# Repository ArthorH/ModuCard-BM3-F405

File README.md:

# Base module (Card) template project for ModuCard System

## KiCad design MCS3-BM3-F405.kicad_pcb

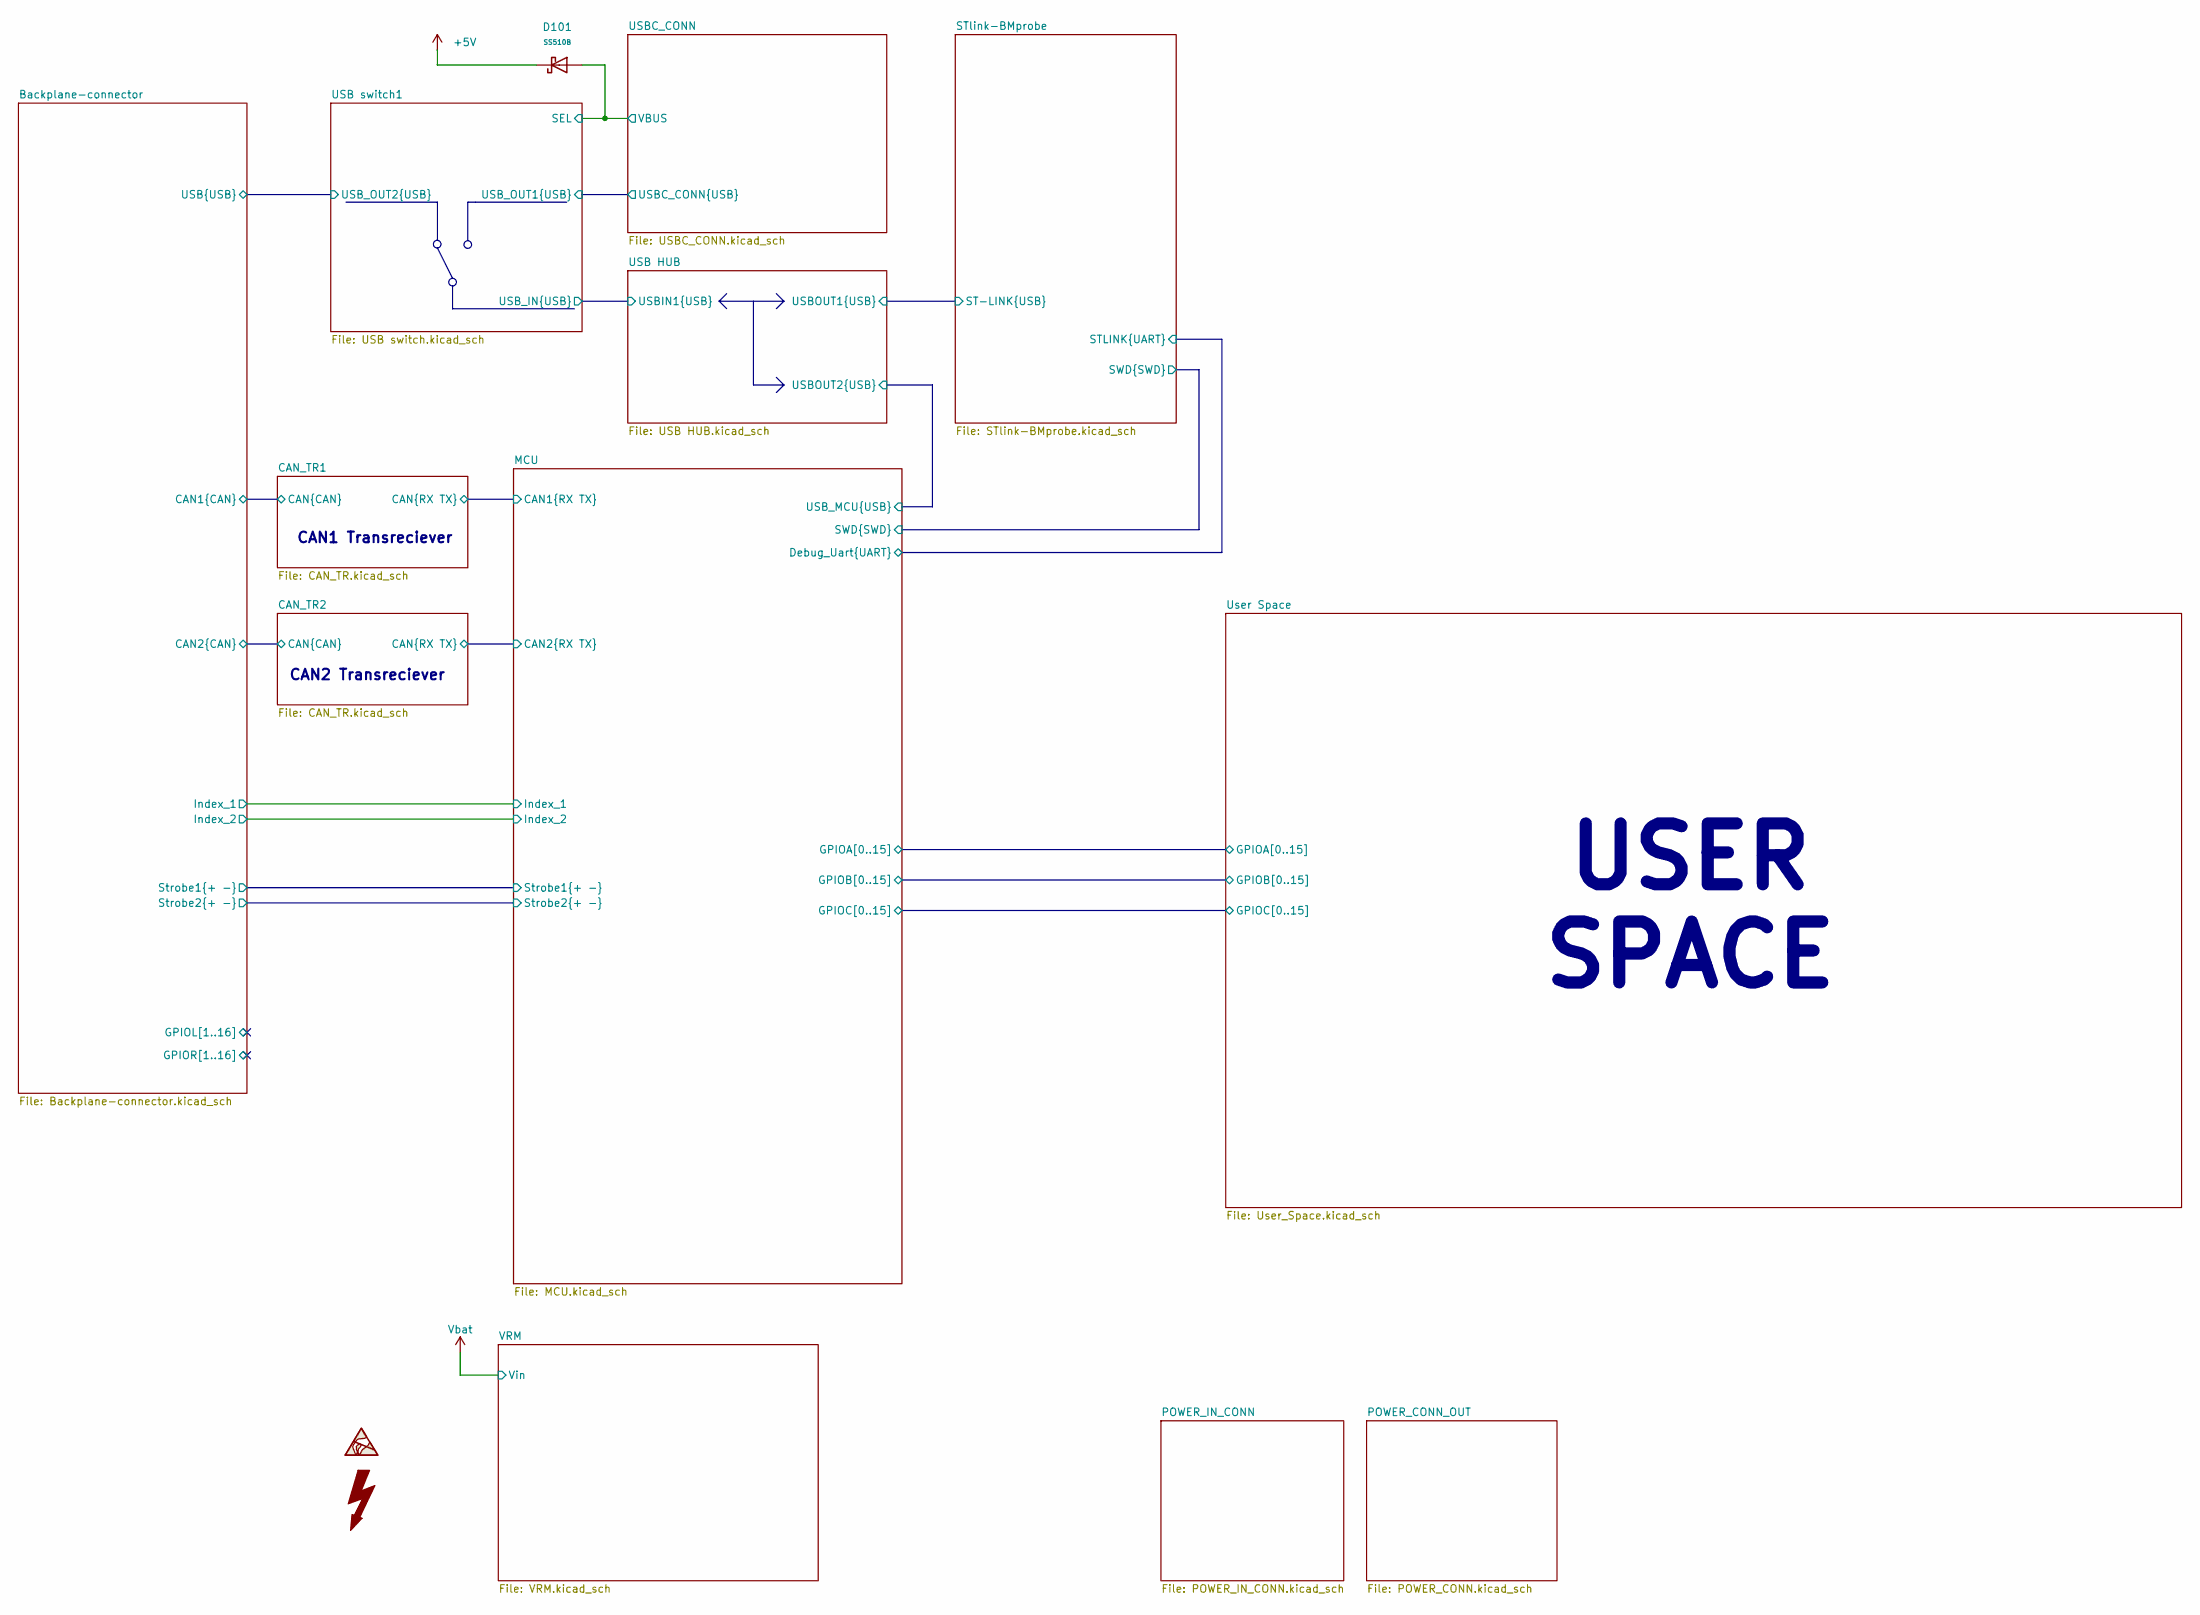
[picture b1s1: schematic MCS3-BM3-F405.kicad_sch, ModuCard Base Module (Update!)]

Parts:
D101: SS510B; D_SMB; Forward Voltage (Vf@If) 0.85V@5.0A; Reverse Voltage (Vr) 100V; Part SS510B; LCSC C7420368

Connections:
+5V: D101.1; also elsewhere on the board
VBUS: D101.2; also elsewhere on the board

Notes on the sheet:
USER SPACE
CAN2 Transreciever
CAN1 Transreciever

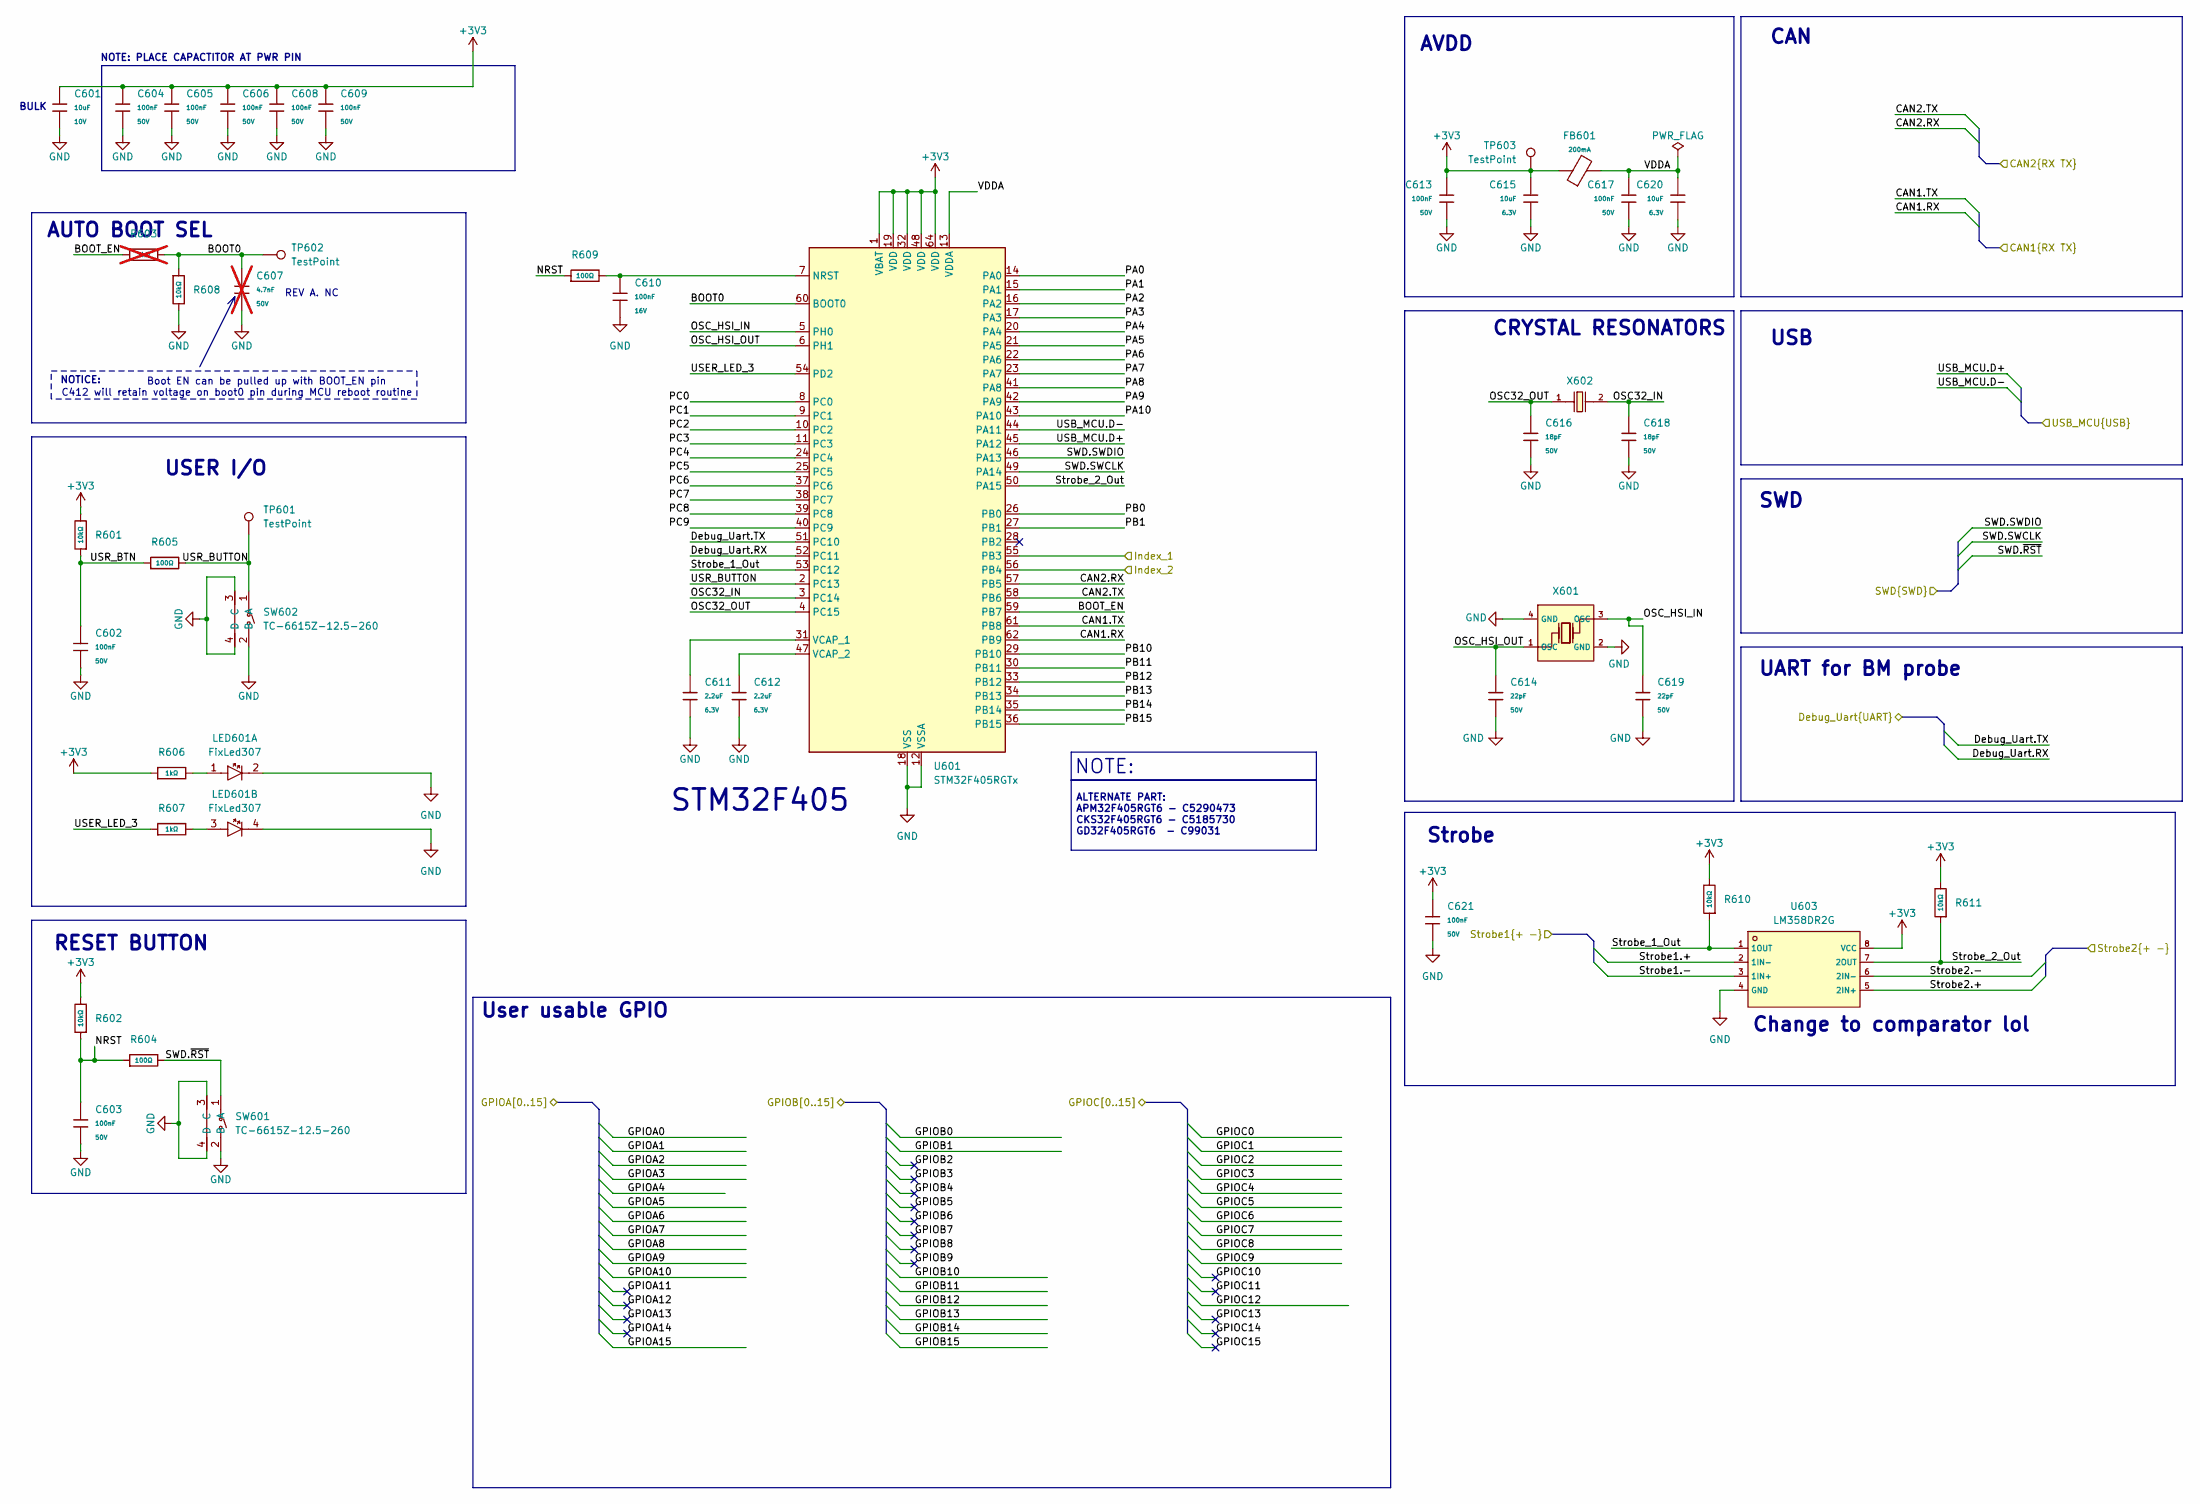
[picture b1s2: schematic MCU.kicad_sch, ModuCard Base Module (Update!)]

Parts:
C601: 10uF; C_0603; Voltage Rated 10V; Tolerance ±10%; Part CL10A106KP8NNNC; LCSC C19702
C602, C603, C604, C605, C606, C608, C609, C613, C617, C621: 100nF; C_0402; Voltage Rated 50V; Tolerance ±10%; Part CL05B104KB54PNC; LCSC C307331
C607: 4.7nF; C_0402; Voltage Rated 50V; Tolerance ±10%; Part 0402B472K500NT; LCSC C1538; not fitted
C610: 100nF; C_0402; Voltage Rated 16V; Tolerance ±10%; Part CL05B104KO5NNNC; LCSC C1525
C611, C612: 2.2uF; C_0402; Voltage Rated 6.3V; Tolerance ±20%; Part CL05A225MQ5NSNC; LCSC C12530
C614, C619: 22pF; C_0402; Voltage Rated 50V; Tolerance ±5%; Part 0402CG220J500NT; LCSC C1555
C615, C620: 10uF; C_0402; Voltage Rated 6.3V; Tolerance ±20%; Part CL05A106MQ5NUNC; LCSC C15525
C616, C618: 18pF; C_0402; Voltage Rated 50V; Tolerance ±5%; Part 0402CG180J500NT; LCSC C1549
FB601: FB_0603; Current Rating 200mA; Tolerance ±25%; Part GZ1608D601TF; LCSC C1002
LED601: FixLed307
R601, R602, R608, R610, R611: 10kΩ; R_0402; Overload Voltage (Max) 50V; Tolerance ±1%; Part 0402WGF1002TCE; LCSC C25744
R603: 1kΩ; R_0402; Overload Voltage (Max) 50V; Tolerance ±1%; Part 0402WGF1001TCE; LCSC C11702; not fitted
R604, R605, R609: 100Ω; R_0402; Overload Voltage (Max) 50V; Tolerance ±1%; Part 0402WGF1000TCE; LCSC C25076
R606, R607: 1kΩ; R_0402; Overload Voltage (Max) 50V; Tolerance ±1%; Part 0402WGF1001TCE; LCSC C11702
SW601, SW602: TC-6615Z-12.5-260; SW-TH_4P-L7.3-TC-6615Z-12.5-260; MPN TC-6615Z-12.5-260; LCSC Part C7528758
TP601, TP602, TP603: TestPoint; TestPoint_Pad_D1.0mm
U601: STM32F405RGTx; LQFP-64_10x10mm_P0.5mm; LCSC C15742
U603: LM358DR2G; SOIC-8_L5.0-W4.0-P1.27-LS6.0-BL; Part LM358DR2G; LCSC C7950
X601: X32258MOB4SI; OSC-SMD_4P-L3.2-W2.5-BL; Frequency Tolerance ±10ppm; Part X322525MOB4SI; LCSC C2682775
X602: Q13FC1350000400; FC-135R_L3.2-W1.5; Frequency Tolerance ±20ppm; Part Q13FC13500004; LCSC C97606

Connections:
+3V3: C601.1, C604.1, C605.1, C606.1, C608.1, C609.1, C613.1, C615.1, C621.1, FB601.1, R601.2, R602.2, R606.1, R610.2, R611.2, TP603.1, U601.1 (VBAT), U601.19 (VDD), U601.32 (VDD), U601.48 (VDD), U601.64 (VDD), U603.8 (VCC); also elsewhere on the board
/Backplane-connector/Index_1: U601.55 (PB3); also elsewhere on the board
/Backplane-connector/Index_2: U601.56 (PB4); also elsewhere on the board
/Backplane-connector/Strobe1.+: U603.2 (1IN-); also elsewhere on the board
/Backplane-connector/Strobe1.-: U603.3 (1IN+); also elsewhere on the board
/Backplane-connector/Strobe2.+: U603.5 (2IN+); also elsewhere on the board
/Backplane-connector/Strobe2.-: U603.6 (2IN-); also elsewhere on the board
/CAN_TR1/CAN.RX: U601.62 (PB9); also elsewhere on the board
/CAN_TR1/CAN.TX: U601.61 (PB8); also elsewhere on the board
/CAN_TR2/CAN.RX: U601.57 (PB5); also elsewhere on the board
/CAN_TR2/CAN.TX: U601.58 (PB6); also elsewhere on the board
/MCU/BOOT0: C607.1, R603.2, R608.1, TP602.1, U601.60 (BOOT0)
/MCU/BOOT_EN: R603.1, U601.59 (PB7)
/MCU/Debug_Uart.RX: U601.52 (PC11); also elsewhere on the board
/MCU/Debug_Uart.TX: U601.51 (PC10); also elsewhere on the board
/MCU/NRST: C603.1, R602.1, R604.1, R609.1
/MCU/OSC32_IN: C618.1, U601.3 (PC14), X602.2
/MCU/OSC32_OUT: C616.1, U601.4 (PC15), X602.1
/MCU/OSC_HSI_IN: C619.1, U601.5 (PH0), X601.3 (OSC)
/MCU/OSC_HSI_OUT: C614.1, U601.6 (PH1), X601.1 (OSC)
/MCU/PA0: U601.14 (PA0)
/MCU/PA1: U601.15 (PA1)
/MCU/PA2: U601.16 (PA2)
/MCU/PA3: U601.17 (PA3)
/MCU/PA4: U601.20 (PA4)
/MCU/PA5: U601.21 (PA5)
/MCU/PA6: U601.22 (PA6)
/MCU/PA7: U601.23 (PA7)
/MCU/PA8: U601.41 (PA8)
/MCU/PA9: U601.42 (PA9)
/MCU/PA10: U601.43 (PA10)
/MCU/PB0: U601.26 (PB0)
/MCU/PB1: U601.27 (PB1)
/MCU/PB10: U601.29 (PB10)
/MCU/PB11: U601.30 (PB11)
/MCU/PB12: U601.33 (PB12)
/MCU/PB13: U601.34 (PB13)
/MCU/PB14: U601.35 (PB14)
/MCU/PB15: U601.36 (PB15)
/MCU/PC0: U601.8 (PC0)
/MCU/PC1: U601.9 (PC1)
/MCU/PC2: U601.10 (PC2)
/MCU/PC3: U601.11 (PC3)
/MCU/PC4: U601.24 (PC4)
/MCU/PC5: U601.25 (PC5)
/MCU/PC6: U601.37 (PC6)
/MCU/PC7: U601.38 (PC7)
/MCU/PC8: U601.39 (PC8)
/MCU/PC9: U601.40 (PC9)
/MCU/SWD.SWCLK: U601.49 (PA14); also elsewhere on the board
/MCU/SWD.SWDIO: U601.46 (PA13); also elsewhere on the board
/MCU/SWD.~RST: R604.2, SW601.1 (A); also elsewhere on the board
/MCU/Strobe_1_Out: R610.1, U601.53 (PC12), U603.1 (1OUT)
/MCU/Strobe_2_Out: R611.1, U601.50 (PA15), U603.7 (2OUT)
/MCU/USB_MCU.D+: U601.45 (PA12); also elsewhere on the board
/MCU/USB_MCU.D-: U601.44 (PA11); also elsewhere on the board
/MCU/USER_LED_3: R607.1, U601.54 (PD2)
/MCU/USR_BTN: C602.1, R601.1, R605.1
/MCU/USR_BUTTON: R605.2, SW602.1 (A), TP601.1 (1_1), U601.2 (PC13)
/MCU/VDDA: C617.1, C620.1, FB601.2, U601.13 (VDDA)
GND: C601.2, C602.2, C603.2, C604.2, C605.2, C606.2, C607.2, C608.2, C609.2, C610.2, C611.2, C612.2, C613.2, C614.2, C615.2, C616.2, C617.2, C618.2, C619.2, C620.2, C621.2, LED601.2, LED601.4, R608.2, SW601.2 (B), SW601.3 (C), SW601.4 (D), SW602.2 (B), SW602.3 (C), SW602.4 (D), U601.12 (VSSA), U601.18 (VSS), U601.63 (VSS), U603.4 (GND), X601.2 (GND), X601.4 (GND); also elsewhere on the board
unnamed: LED601.1, R606.2
unnamed: LED601.3, R607.2
unnamed: C610.1, R609.2, U601.7 (NRST)
unnamed: C611.1, U601.31 (VCAP_1)
unnamed: C612.1, U601.47 (VCAP_2)

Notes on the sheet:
AUTO BOOT SEL
Boot EN can be pulled up with BOOT_EN pin C412 will retain voltage on boot0 pin during MCU reboot routine
USER I/O
STM32F405
NOTE: PLACE CAPACTITOR AT PWR PIN
AVDD
RESET BUTTON
REV A. NC
Strobe
CAN
USB
CRYSTAL RESONATORS
Change to comparator lol
User usable GPIO
BULK
NOTICE:
UART for BM probe
ALTERNATE PART: APM32F405RGT6 - C5290473 CKS32F405RGT6 - C5185730 GD32F405RGT6 - C99031
SWD
NOTE:

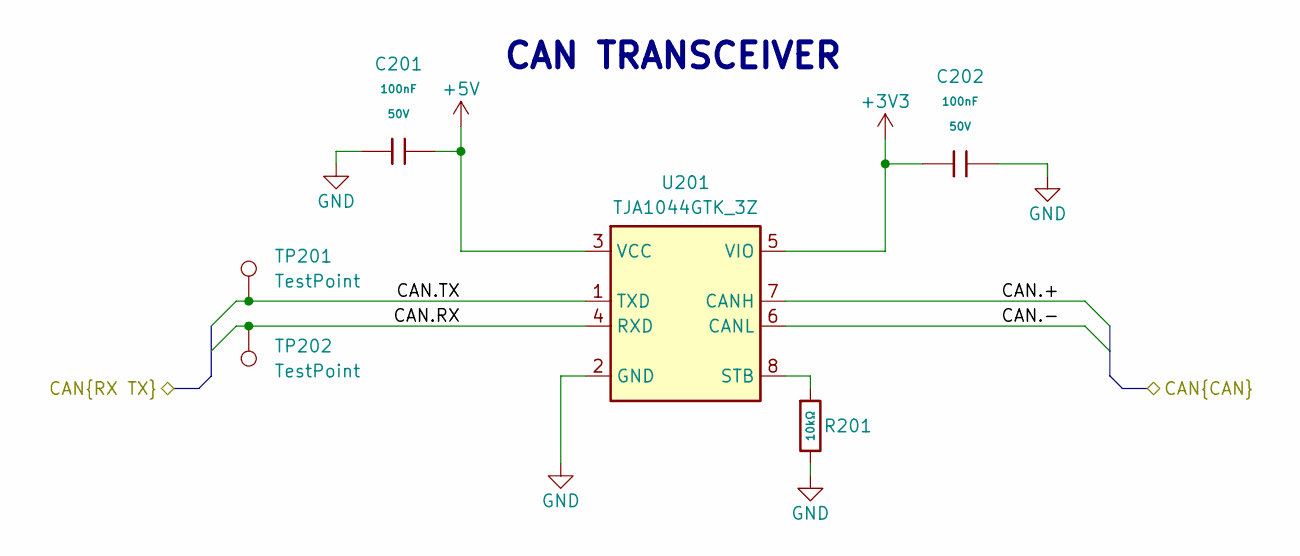
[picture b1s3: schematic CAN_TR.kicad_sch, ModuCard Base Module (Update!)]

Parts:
C201, C202: 100nF; C_0402; Voltage Rated 50V; Tolerance ±10%; Part CL05B104KB54PNC; LCSC C307331
R201: 10kΩ; R_0402; Overload Voltage (Max) 50V; Tolerance ±1%; Part 0402WGF1002TCE; LCSC C25744
TP201, TP202: TestPoint; TestPoint_Pad_D1.0mm
U201: TJA1044GTK_3Z; HVSON-8-1EP_3x3mm_P0.65mm_EP1.6x2.4mm; Manufacturer_Part_Number TJA1044GTK/3Z; LCSC C5215851

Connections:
+3V3: C202.1, U201.5 (VIO); also elsewhere on the board
+5V: C201.2, U201.3 (VCC); also elsewhere on the board
/Backplane-connector/CAN1.+: U201.7 (CANH); also elsewhere on the board
/Backplane-connector/CAN1.-: U201.6 (CANL); also elsewhere on the board
/CAN_TR1/CAN.RX: U201.4 (RXD); also elsewhere on the board
/CAN_TR1/CAN.TX: U201.1 (TXD); also elsewhere on the board
GND: C201.1, C202.2, R201.2, U201.2 (GND), U201.9 (EP); also elsewhere on the board
unnamed: R201.1, U201.8 (STB)

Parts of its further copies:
C301, C302: 100nF; C_0402; Voltage Rated 50V; Tolerance ±10%; Part CL05B104KB54PNC; LCSC C307331
R301: 10kΩ; R_0402; Overload Voltage (Max) 50V; Tolerance ±1%; Part 0402WGF1002TCE; LCSC C25744
U301: TJA1044GTK_3Z; HVSON-8-1EP_3x3mm_P0.65mm_EP1.6x2.4mm; Manufacturer_Part_Number TJA1044GTK/3Z; LCSC C5215851

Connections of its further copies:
+3V3: C302.1, U301.5 (VIO); also elsewhere on the board
+5V: C301.2, U301.3 (VCC); also elsewhere on the board
/Backplane-connector/CAN2.+: U301.7 (CANH); also elsewhere on the board
/Backplane-connector/CAN2.-: U301.6 (CANL); also elsewhere on the board
/CAN_TR2/CAN.RX: U301.4 (RXD); also elsewhere on the board
/CAN_TR2/CAN.TX: U301.1 (TXD); also elsewhere on the board
GND: C301.1, C302.2, R301.2, U301.2 (GND), U301.9 (EP); also elsewhere on the board
unnamed: R301.1, U301.8 (STB)

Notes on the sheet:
CAN TRANSCEIVER

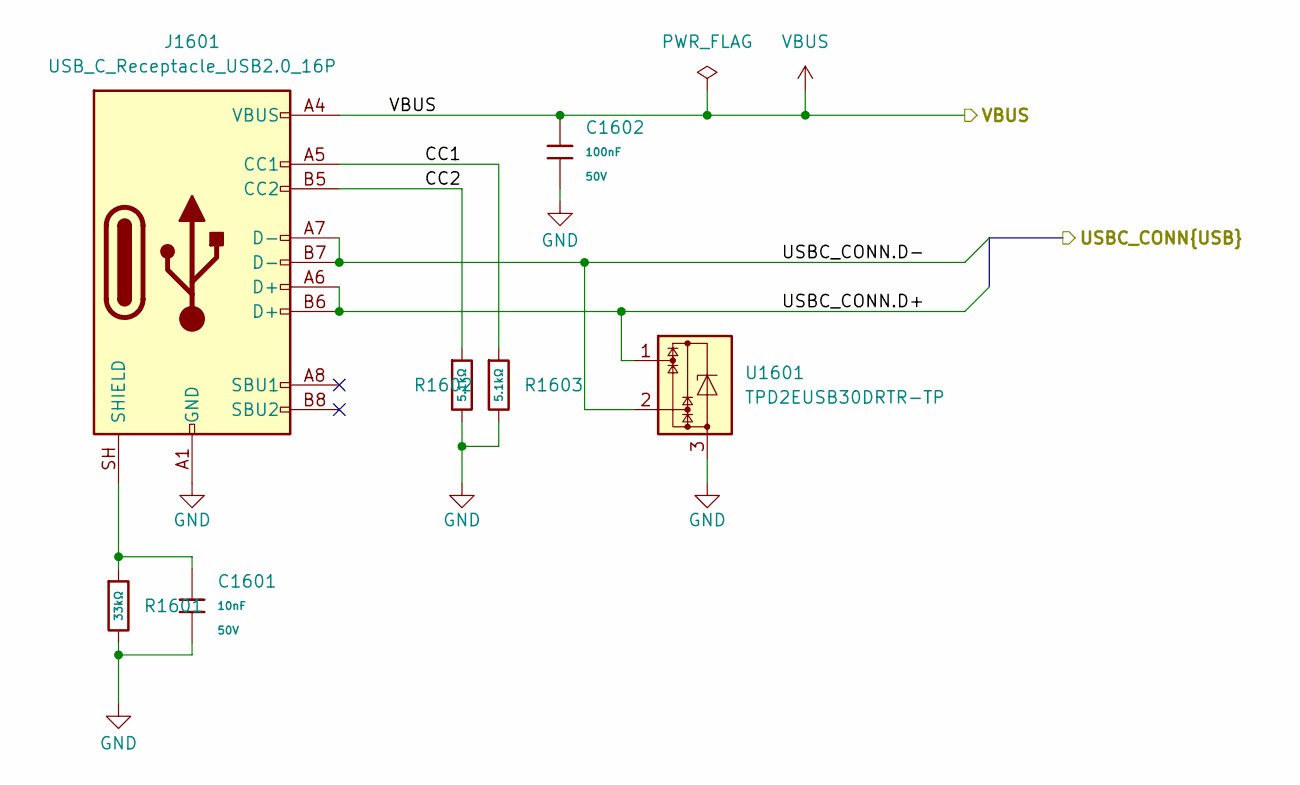
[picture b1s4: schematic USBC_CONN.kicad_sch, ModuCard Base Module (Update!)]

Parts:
C1601: 10nF; C_0402; Voltage Rated 50V; Tolerance ±10%; Part CL05B103KB5NNNC; LCSC C15195
C1602: 100nF; C_0402; Voltage Rated 50V; Tolerance ±10%; Part CL05B104KB54PNC; LCSC C307331
J1601: USB_C_Receptacle_USB2.0_16P; USB_C_Receptacle_GCT_USB4105-xx-A_16P_TopMnt_Horizontal; LCSC C165948
R1601: 33kΩ; R_0402; Overload Voltage (Max) 50V; Tolerance ±1%; Part 0402WGF3302TCE; LCSC C25779
R1602, R1603: 5.1kΩ; R_0402; Overload Voltage (Max) 50V; Tolerance ±1%; Part 0402WGF5101TCE; LCSC C25905
U1601: TPD2EUSB30DRTR-TP; SOT-723; LCSC C2844720

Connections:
/USB switch1/USB_OUT1.D+: J1601.A6 (D+), J1601.B6 (D+), U1601.1; also elsewhere on the board
/USB switch1/USB_OUT1.D-: J1601.A7 (D-), J1601.B7 (D-), U1601.2; also elsewhere on the board
/USBC_CONN/CC1: J1601.A5 (CC1), R1603.1
/USBC_CONN/CC2: J1601.B5 (CC2), R1602.1
GND: C1601.2, C1602.2, J1601.A1 (GND), J1601.A12 (GND), J1601.B1 (GND), J1601.B12 (GND), R1601.2, R1602.2, R1603.2, U1601.3; also elsewhere on the board
unnamed: C1601.1, J1601.SH (SHIELD), R1601.1
VBUS: C1602.1, J1601.A4 (VBUS), J1601.A9 (VBUS), J1601.B4 (VBUS), J1601.B9 (VBUS); also elsewhere on the board

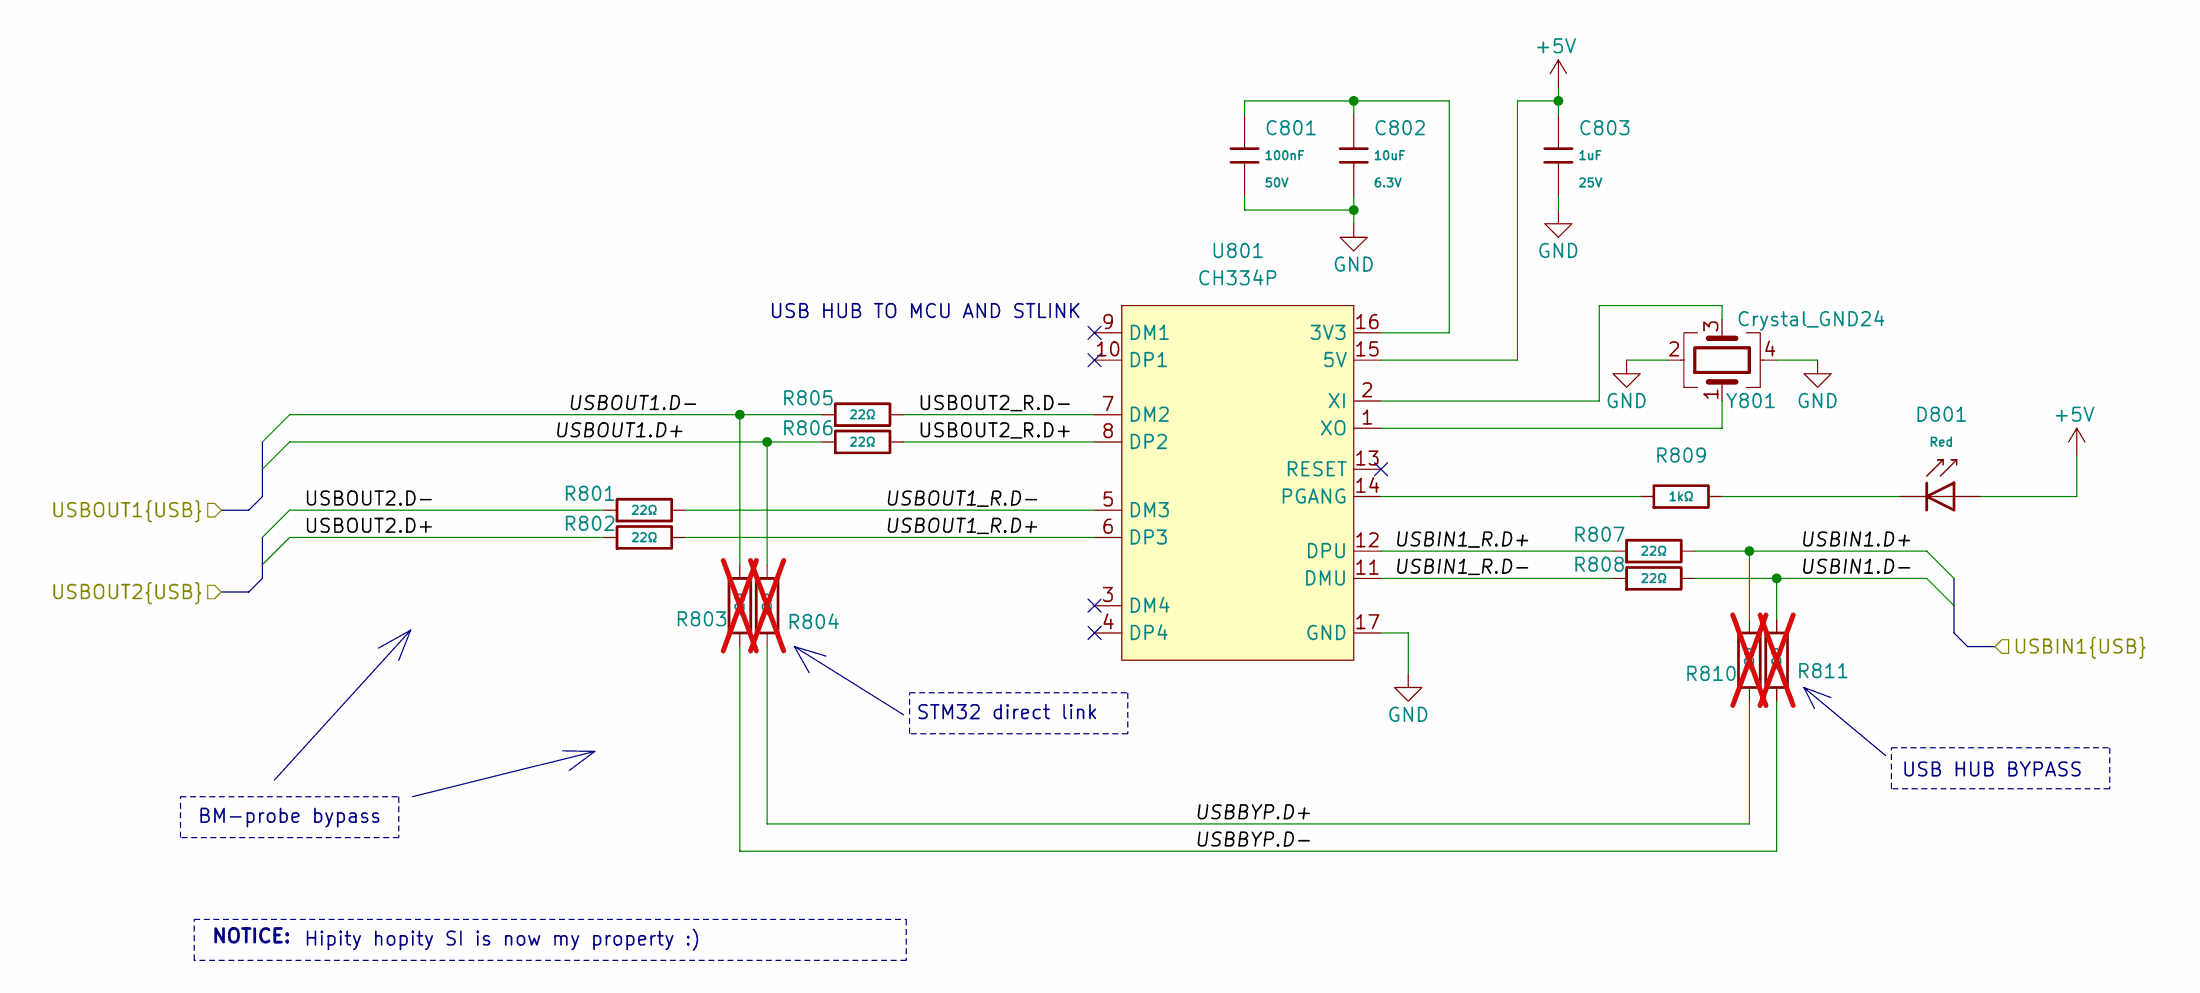
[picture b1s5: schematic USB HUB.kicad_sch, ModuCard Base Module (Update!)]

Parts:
C801: 100nF; C_0402; Voltage Rated 50V; Tolerance ±10%; Part CL05B104KB54PNC; LCSC C307331
C802: 10uF; C_0402; Voltage Rated 6.3V; Tolerance ±20%; Part CL05A106MQ5NUNC; LCSC C15525
C803: 1uF; C_0402; Voltage Rated 25V; Tolerance ±10%; Part CL05A105KA5NQNC; LCSC C52923
D801: Red; D_0603; Part KT-0603R; LCSC C2286
R801, R802, R805, R806, R807, R808: 22Ω; R_0402; Overload Voltage (Max) 50V; Tolerance ±1%; Part 0402WGF220JTCE; LCSC C25092
R803, R804, R810, R811: 22Ω; R_0402; Overload Voltage (Max) 50V; Tolerance ±1%; Part 0402WGF220JTCE; LCSC C25092; not fitted
R809: 1kΩ; R_0402; Overload Voltage (Max) 50V; Tolerance ±1%; Part 0402WGF1001TCE; LCSC C11702
U801: CH334P; QFN-16-1EP_3x3mm_P0.5mm_EP1.7x1.7mm
Y801: Crystal_GND24; Crystal_SMD_3225-4Pin_3.2x2.5mm; LCSC C9002

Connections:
+5V: C803.1, D801.2, U801.15 (5V); also elsewhere on the board
/MCU/USB_MCU.D+: R802.1; also elsewhere on the board
/MCU/USB_MCU.D-: R801.1; also elsewhere on the board
/STlink-BMprobe/ST-LINK.D+: R804.2, R806.1; also elsewhere on the board
/STlink-BMprobe/ST-LINK.D-: R803.2, R805.1; also elsewhere on the board
/USB HUB/USBBYP.D+: R804.1, R810.1
/USB HUB/USBBYP.D-: R803.1, R811.1
/USB HUB/USBIN1.D+: R807.2, R810.2; also elsewhere on the board
/USB HUB/USBIN1.D-: R808.2, R811.2; also elsewhere on the board
/USB HUB/USBIN1_R.D+: R807.1, U801.12 (DPU)
/USB HUB/USBIN1_R.D-: R808.1, U801.11 (DMU)
/USB HUB/USBOUT1_R.D+: R802.2, U801.6 (DP3)
/USB HUB/USBOUT1_R.D-: R801.2, U801.5 (DM3)
/USB HUB/USBOUT2_R.D+: R806.2, U801.8 (DP2)
/USB HUB/USBOUT2_R.D-: R805.2, U801.7 (DM2)
GND: C801.2, C802.2, C803.2, U801.17 (GND), Y801.2, Y801.4; also elsewhere on the board
unnamed: D801.1, R809.2
unnamed: C801.1, C802.1, U801.16 (3V3)
unnamed: R809.1, U801.14 (PGANG)
unnamed: U801.2 (XI), Y801.3
unnamed: U801.1 (XO), Y801.1

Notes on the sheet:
STM32 direct link
USB HUB BYPASS
BM-probe bypass
Hipity hopity SI is now my property :)
NOTICE:
USB HUB TO MCU AND STLINK

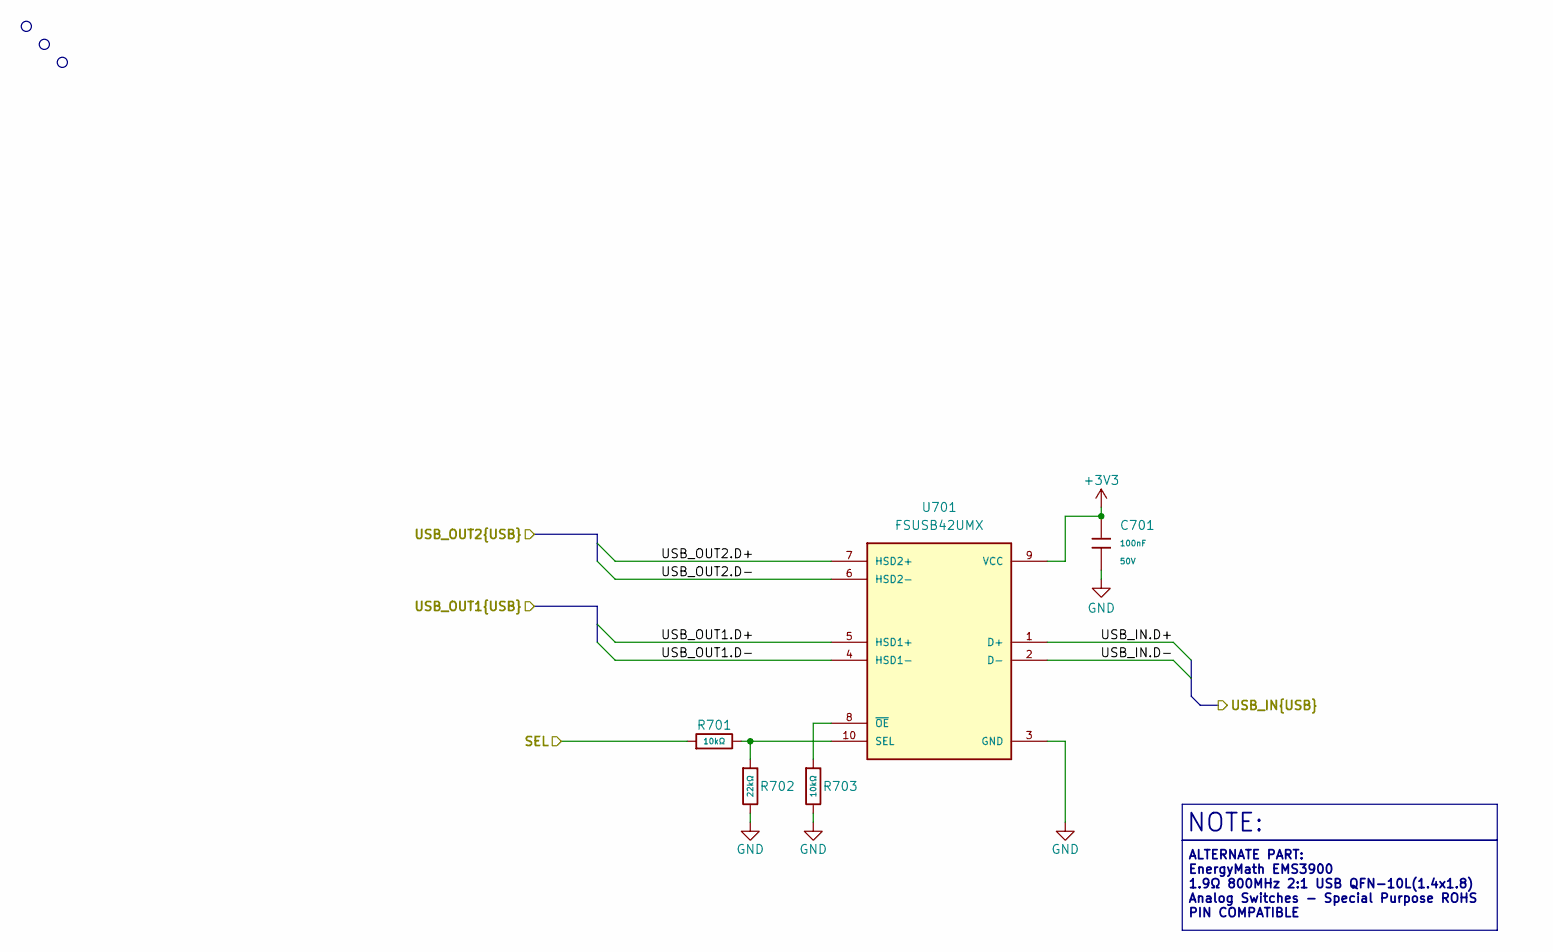
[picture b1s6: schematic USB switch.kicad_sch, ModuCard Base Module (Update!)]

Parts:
C701: 100nF; C_0402; Voltage Rated 50V; Tolerance ±10%; Part CL05B104KB54PNC; LCSC C307331
R701, R703: 10kΩ; R_0402; Overload Voltage (Max) 50V; Tolerance ±1%; Part 0402WGF1002TCE; LCSC C25744
R702: 22kΩ; R_0402; Overload Voltage (Max) 50V; Tolerance ±1%; Part 0402WGF2202TCE; LCSC C25768
U701: FSUSB42UMX; UQFN-10_1.4x1.8mm_P0.4mm; PARTREV 1.25; LCSC C11145

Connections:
+3V3: C701.1, U701.9 (VCC); also elsewhere on the board
/Backplane-connector/USB.D+: U701.7 (HSD2+); also elsewhere on the board
/Backplane-connector/USB.D-: U701.6 (HSD2-); also elsewhere on the board
/USB HUB/USBIN1.D+: U701.1 (D+); also elsewhere on the board
/USB HUB/USBIN1.D-: U701.2 (D-); also elsewhere on the board
/USB switch1/USB_OUT1.D+: U701.5 (HSD1+); also elsewhere on the board
/USB switch1/USB_OUT1.D-: U701.4 (HSD1-); also elsewhere on the board
GND: C701.2, R702.2, R703.2, U701.3 (GND); also elsewhere on the board
unnamed: R701.2, R702.1, U701.10 (SEL)
unnamed: R703.1, U701.8 (~OE)
VBUS: R701.1; also elsewhere on the board

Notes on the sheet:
ALTERNATE PART: EnergyMath EMS3900 1.9Ω 800MHz 2:1 USB QFN-10L(1.4x1.8) Analog Switches - Special Purpose ROHS PIN COMPATIBLE
NOTE:
